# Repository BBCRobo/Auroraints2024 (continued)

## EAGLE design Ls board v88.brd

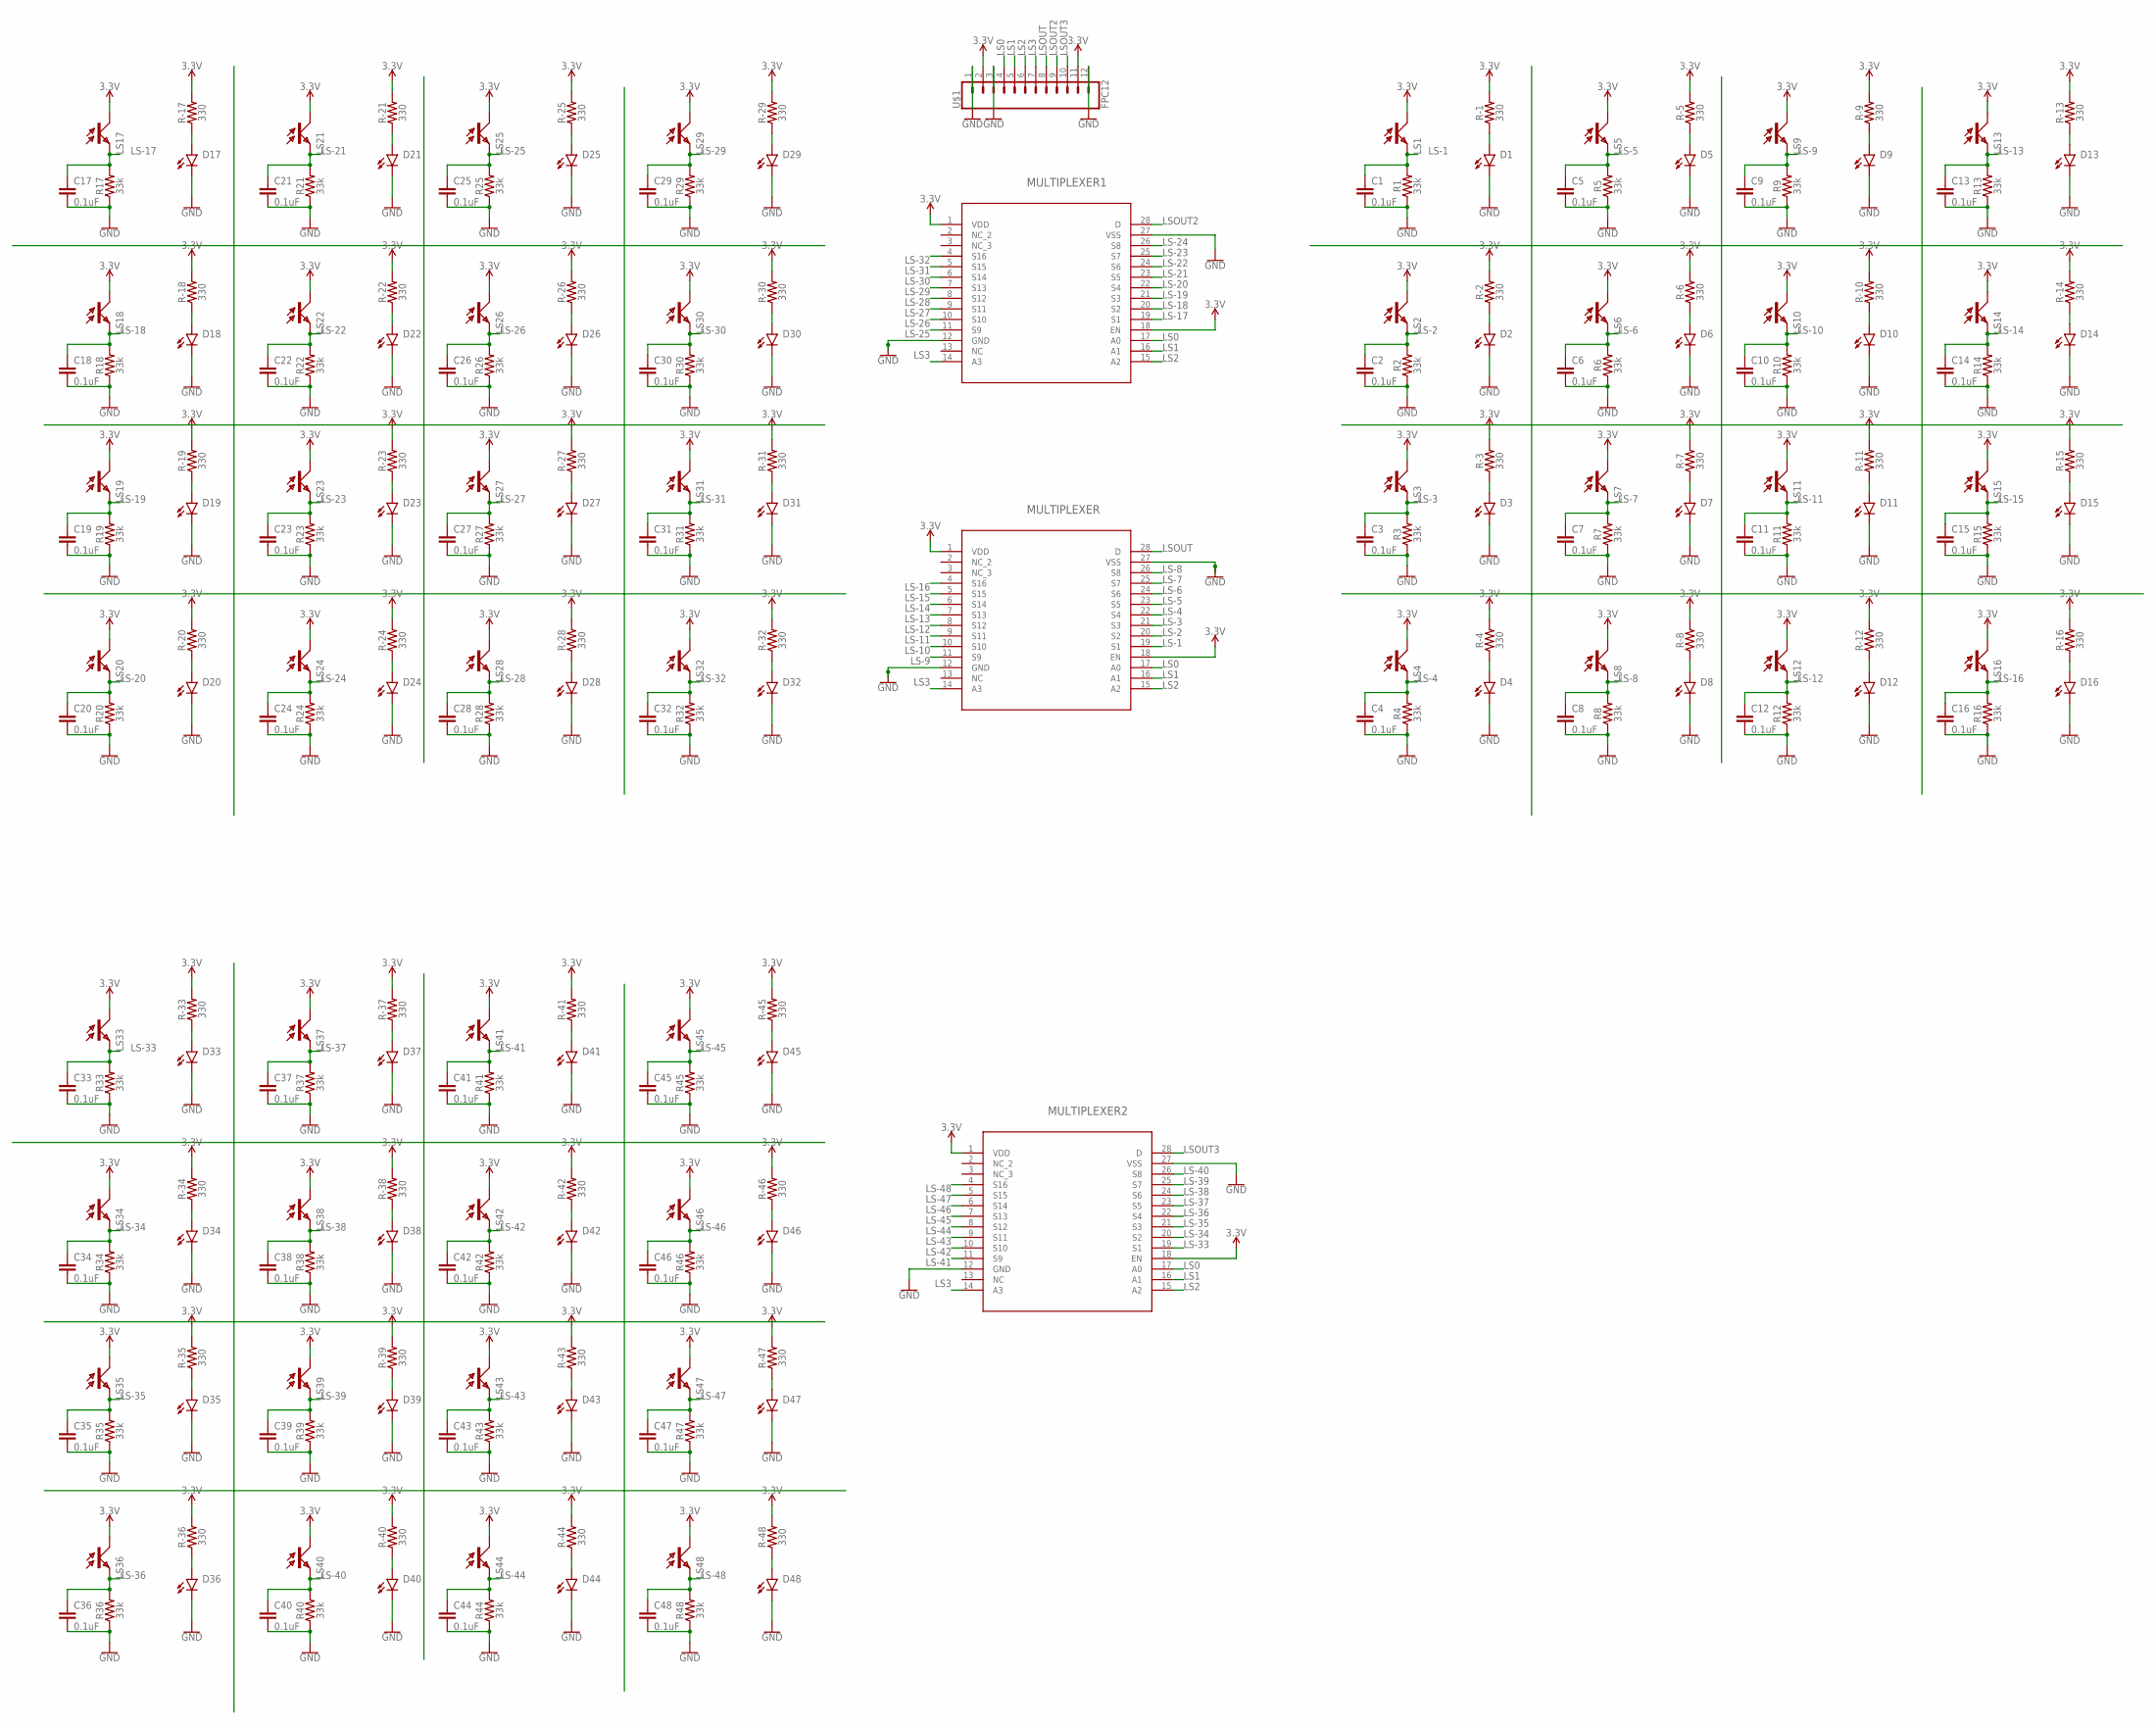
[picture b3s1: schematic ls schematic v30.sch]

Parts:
C1, C2, C3, C4, C5, C6, C7, C8, C9, C10, C11, C12, C13, C14, C15, C16, C17, C18, C19, C20, C21, C22, C23, C24, C25, C26, C27, C28, C29, C30, C31, C32, C33, C34, C35, C36, C37, C38, C39, C40, C41, C42, C43, C44, C45, C46, C47, C48: 0.1uF; 0603
D1, D2, D3, D4, D5, D6, D7, D8, D9, D10, D11, D12, D13, D14, D15, D16, D17, D18, D19, D20, D21, D22, D23, D24, D25, D26, D27, D28, D29, D30, D31, D32, D33, D34, D35, D36, D37, D38, D39, D40, D41, D42, D43, D44, D45, D46, D47, D48: CHIP-FLAT-B_0603-0.35MM; LEDC1608X35N_FLAT-B
LS1, LS2, LS3, LS4, LS5, LS6, LS7, LS8, LS9, LS10, LS11, LS12, LS13, LS14, LS15, LS16, LS17, LS18, LS19, LS20, LS21, LS22, LS23, LS24, LS25, LS26, LS27, LS28, LS29, LS30, LS31, LS32, LS33, LS34, LS35, LS36, LS37, LS38, LS39, LS40, LS41, LS42, LS43, LS44, LS45, LS46, LS47, LS48: ALS; SMD
MULTIPLEXER, MULTIPLEXER1, MULTIPLEXER2: ADG1206YRUZRU_28_ADI-L; RU_28_ADI-L
R1, R2, R3, R4, R5, R6, R7, R8, R9, R10, R11, R12, R13, R14, R15, R16, R17, R18, R19, R20, R21, R22, R23, R24, R25, R26, R27, R28, R29, R30, R31, R32, R33, R34, R35, R36, R37, R38, R39, R40, R41, R42, R43, R44, R45, R46, R47, R48: 33k; 0603
R-1, R-2, R-3, R-4, R-5, R-6, R-7, R-8, R-9, R-10, R-11, R-12, R-13, R-14, R-15, R-16, R-17, R-18, R-19, R-20, R-21, R-22, R-23, R-24, R-25, R-26, R-27, R-28, R-29, R-30, R-31, R-32, R-33, R-34, R-35, R-36, R-37, R-38, R-39, R-40, R-41, R-42, R-43, R-44, R-45, R-46, R-47, R-48: 330; 0603
U$1: FPC12

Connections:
3.3V: LS1.C, LS2.C, LS3.C, LS4.C, LS5.C, LS6.C, LS7.C, LS8.C, LS9.C, LS10.C, LS11.C, LS12.C, LS13.C, LS14.C, LS15.C, LS16.C, LS17.C, LS18.C, LS19.C, LS20.C, LS21.C, LS22.C, LS23.C, LS24.C, LS25.C, LS26.C, LS27.C, LS28.C, LS29.C, LS30.C, LS31.C, LS32.C, LS33.C, LS34.C, LS35.C, LS36.C, LS37.C, LS38.C, LS39.C, LS40.C, LS41.C, LS42.C, LS43.C, LS44.C, LS45.C, LS46.C, LS47.C, LS48.C, MULTIPLEXER.1 (VDD), MULTIPLEXER.18 (EN), MULTIPLEXER1.1 (VDD), MULTIPLEXER1.18 (EN), MULTIPLEXER2.1 (VDD), MULTIPLEXER2.18 (EN), R-1.2, R-2.2, R-3.2, R-4.2, R-5.2, R-6.2, R-7.2, R-8.2, R-9.2, R-10.2, R-11.2, R-12.2, R-13.2, R-14.2, R-15.2, R-16.2, R-17.2, R-18.2, R-19.2, R-20.2, R-21.2, R-22.2, R-23.2, R-24.2, R-25.2, R-26.2, R-27.2, R-28.2, R-29.2, R-30.2, R-31.2, R-32.2, R-33.2, R-34.2, R-35.2, R-36.2, R-37.2, R-38.2, R-39.2, R-40.2, R-41.2, R-42.2, R-43.2, R-44.2, R-45.2, R-46.2, R-47.2, R-48.2, U$1.2, U$1.11
GND: C1.2, C2.2, C3.2, C4.2, C5.2, C6.2, C7.2, C8.2, C9.2, C10.2, C11.2, C12.2, C13.2, C14.2, C15.2, C16.2, C17.2, C18.2, C19.2, C20.2, C21.2, C22.2, C23.2, C24.2, C25.2, C26.2, C27.2, C28.2, C29.2, C30.2, C31.2, C32.2, C33.2, C34.2, C35.2, C36.2, C37.2, C38.2, C39.2, C40.2, C41.2, C42.2, C43.2, C44.2, C45.2, C46.2, C47.2, C48.2, D1.C, D2.C, D3.C, D4.C, D5.C, D6.C, D7.C, D8.C, D9.C, D10.C, D11.C, D12.C, D13.C, D14.C, D15.C, D16.C, D17.C, D18.C, D19.C, D20.C, D21.C, D22.C, D23.C, D24.C, D25.C, D26.C, D27.C, D28.C, D29.C, D30.C, D31.C, D32.C, D33.C, D34.C, D35.C, D36.C, D37.C, D38.C, D39.C, D40.C, D41.C, D42.C, D43.C, D44.C, D45.C, D46.C, D47.C, D48.C, MULTIPLEXER.12 (GND), MULTIPLEXER.27 (VSS), MULTIPLEXER1.12 (GND), MULTIPLEXER1.27 (VSS), MULTIPLEXER2.12 (GND), MULTIPLEXER2.27 (VSS), R1.1, R2.1, R3.1, R4.1, R5.1, R6.1, R7.1, R8.1, R9.1, R10.1, R11.1, R12.1, R13.1, R14.1, R15.1, R16.1, R17.1, R18.1, R19.1, R20.1, R21.1, R22.1, R23.1, R24.1, R25.1, R26.1, R27.1, R28.1, R29.1, R30.1, R31.1, R32.1, R33.1, R34.1, R35.1, R36.1, R37.1, R38.1, R39.1, R40.1, R41.1, R42.1, R43.1, R44.1, R45.1, R46.1, R47.1, R48.1, U$1.1, U$1.3, U$1.12
LS0: MULTIPLEXER.17 (A0), MULTIPLEXER1.17 (A0), MULTIPLEXER2.17 (A0), U$1.4
LS1: MULTIPLEXER.16 (A1), MULTIPLEXER1.16 (A1), MULTIPLEXER2.16 (A1), U$1.5
LS2: MULTIPLEXER.15 (A2), MULTIPLEXER1.15 (A2), MULTIPLEXER2.15 (A2), U$1.6
LS3: MULTIPLEXER.14 (A3), MULTIPLEXER1.14 (A3), MULTIPLEXER2.14 (A3), U$1.7
LS-1: C1.1, LS1.E, MULTIPLEXER.19 (S1), R1.2
LS-2: C2.1, LS2.E, MULTIPLEXER.20 (S2), R2.2
LS-3: C3.1, LS3.E, MULTIPLEXER.21 (S3), R3.2
LS-4: C4.1, LS4.E, MULTIPLEXER.22 (S4), R4.2
LS-5: C5.1, LS5.E, MULTIPLEXER.23 (S5), R5.2
LS-6: C6.1, LS6.E, MULTIPLEXER.24 (S6), R6.2
LS-7: C7.1, LS7.E, MULTIPLEXER.25 (S7), R7.2
LS-8: C8.1, LS8.E, MULTIPLEXER.26 (S8), R8.2
LS-9: C9.1, LS9.E, MULTIPLEXER.11 (S9), R9.2
LS-10: C10.1, LS10.E, MULTIPLEXER.10 (S10), R10.2
LS-11: C11.1, LS11.E, MULTIPLEXER.9 (S11), R11.2
LS-12: C12.1, LS12.E, MULTIPLEXER.8 (S12), R12.2
LS-13: C13.1, LS13.E, MULTIPLEXER.7 (S13), R13.2
LS-14: C14.1, LS14.E, MULTIPLEXER.6 (S14), R14.2
LS-15: C15.1, LS15.E, MULTIPLEXER.5 (S15), R15.2
LS-16: C16.1, LS16.E, MULTIPLEXER.4 (S16), R16.2
LS-17: C17.1, LS17.E, MULTIPLEXER1.19 (S1), R17.2
LS-18: C18.1, LS18.E, MULTIPLEXER1.20 (S2), R18.2
LS-19: C19.1, LS19.E, MULTIPLEXER1.21 (S3), R19.2
LS-20: C20.1, LS20.E, MULTIPLEXER1.22 (S4), R20.2
LS-21: C21.1, LS21.E, MULTIPLEXER1.23 (S5), R21.2
LS-22: C22.1, LS22.E, MULTIPLEXER1.24 (S6), R22.2
LS-23: C23.1, LS23.E, MULTIPLEXER1.25 (S7), R23.2
LS-24: C24.1, LS24.E, MULTIPLEXER1.26 (S8), R24.2
LS-25: C25.1, LS25.E, MULTIPLEXER1.11 (S9), R25.2
LS-26: C26.1, LS26.E, MULTIPLEXER1.10 (S10), R26.2
LS-27: C27.1, LS27.E, MULTIPLEXER1.9 (S11), R27.2
LS-28: C28.1, LS28.E, MULTIPLEXER1.8 (S12), R28.2
LS-29: C29.1, LS29.E, MULTIPLEXER1.7 (S13), R29.2
LS-30: C30.1, LS30.E, MULTIPLEXER1.6 (S14), R30.2
LS-31: C31.1, LS31.E, MULTIPLEXER1.5 (S15), R31.2
LS-32: C32.1, LS32.E, MULTIPLEXER1.4 (S16), R32.2
LS-33: C33.1, LS33.E, MULTIPLEXER2.19 (S1), R33.2
LS-34: C34.1, LS34.E, MULTIPLEXER2.20 (S2), R34.2
LS-35: C35.1, LS35.E, MULTIPLEXER2.21 (S3), R35.2
LS-36: C36.1, LS36.E, MULTIPLEXER2.22 (S4), R36.2
LS-37: C37.1, LS37.E, MULTIPLEXER2.23 (S5), R37.2
LS-38: C38.1, LS38.E, MULTIPLEXER2.24 (S6), R38.2
LS-39: C39.1, LS39.E, MULTIPLEXER2.25 (S7), R39.2
LS-40: C40.1, LS40.E, MULTIPLEXER2.26 (S8), R40.2
LS-41: C41.1, LS41.E, MULTIPLEXER2.11 (S9), R41.2
LS-42: C42.1, LS42.E, MULTIPLEXER2.10 (S10), R42.2
LS-43: C43.1, LS43.E, MULTIPLEXER2.9 (S11), R43.2
LS-44: C44.1, LS44.E, MULTIPLEXER2.8 (S12), R44.2
LS-45: C45.1, LS45.E, MULTIPLEXER2.7 (S13), R45.2
LS-46: C46.1, LS46.E, MULTIPLEXER2.6 (S14), R46.2
LS-47: C47.1, LS47.E, MULTIPLEXER2.5 (S15), R47.2
LS-48: C48.1, LS48.E, MULTIPLEXER2.4 (S16), R48.2
LSOUT: MULTIPLEXER.28 (D), U$1.8
LSOUT2: MULTIPLEXER1.28 (D), U$1.9
LSOUT3: MULTIPLEXER2.28 (D), U$1.10
unnamed: D1.A, R-1.1
unnamed: D2.A, R-2.1
unnamed: D3.A, R-3.1
unnamed: D4.A, R-4.1
unnamed: D5.A, R-5.1
unnamed: D6.A, R-6.1
unnamed: D7.A, R-7.1
unnamed: D8.A, R-8.1
unnamed: D9.A, R-9.1
unnamed: D10.A, R-10.1
unnamed: D11.A, R-11.1
unnamed: D12.A, R-12.1
unnamed: D13.A, R-13.1
unnamed: D14.A, R-14.1
unnamed: D15.A, R-15.1
unnamed: D16.A, R-16.1
unnamed: D17.A, R-17.1
unnamed: D18.A, R-18.1
unnamed: D19.A, R-19.1
unnamed: D20.A, R-20.1
unnamed: D21.A, R-21.1
unnamed: D22.A, R-22.1
unnamed: D23.A, R-23.1
unnamed: D24.A, R-24.1
unnamed: D25.A, R-25.1
unnamed: D26.A, R-26.1
unnamed: D27.A, R-27.1
unnamed: D33.A, R-33.1
unnamed: D34.A, R-34.1
unnamed: D35.A, R-35.1
unnamed: D36.A, R-36.1
unnamed: D37.A, R-37.1
unnamed: D28.A, R-28.1
unnamed: D29.A, R-29.1
unnamed: D30.A, R-30.1
unnamed: D31.A, R-31.1
unnamed: D32.A, R-32.1
unnamed: D38.A, R-38.1
unnamed: D39.A, R-39.1
unnamed: D40.A, R-40.1
unnamed: D41.A, R-41.1
unnamed: D42.A, R-42.1
unnamed: D43.A, R-43.1
unnamed: D44.A, R-44.1
unnamed: D45.A, R-45.1
unnamed: D46.A, R-46.1
unnamed: D47.A, R-47.1
unnamed: D48.A, R-48.1

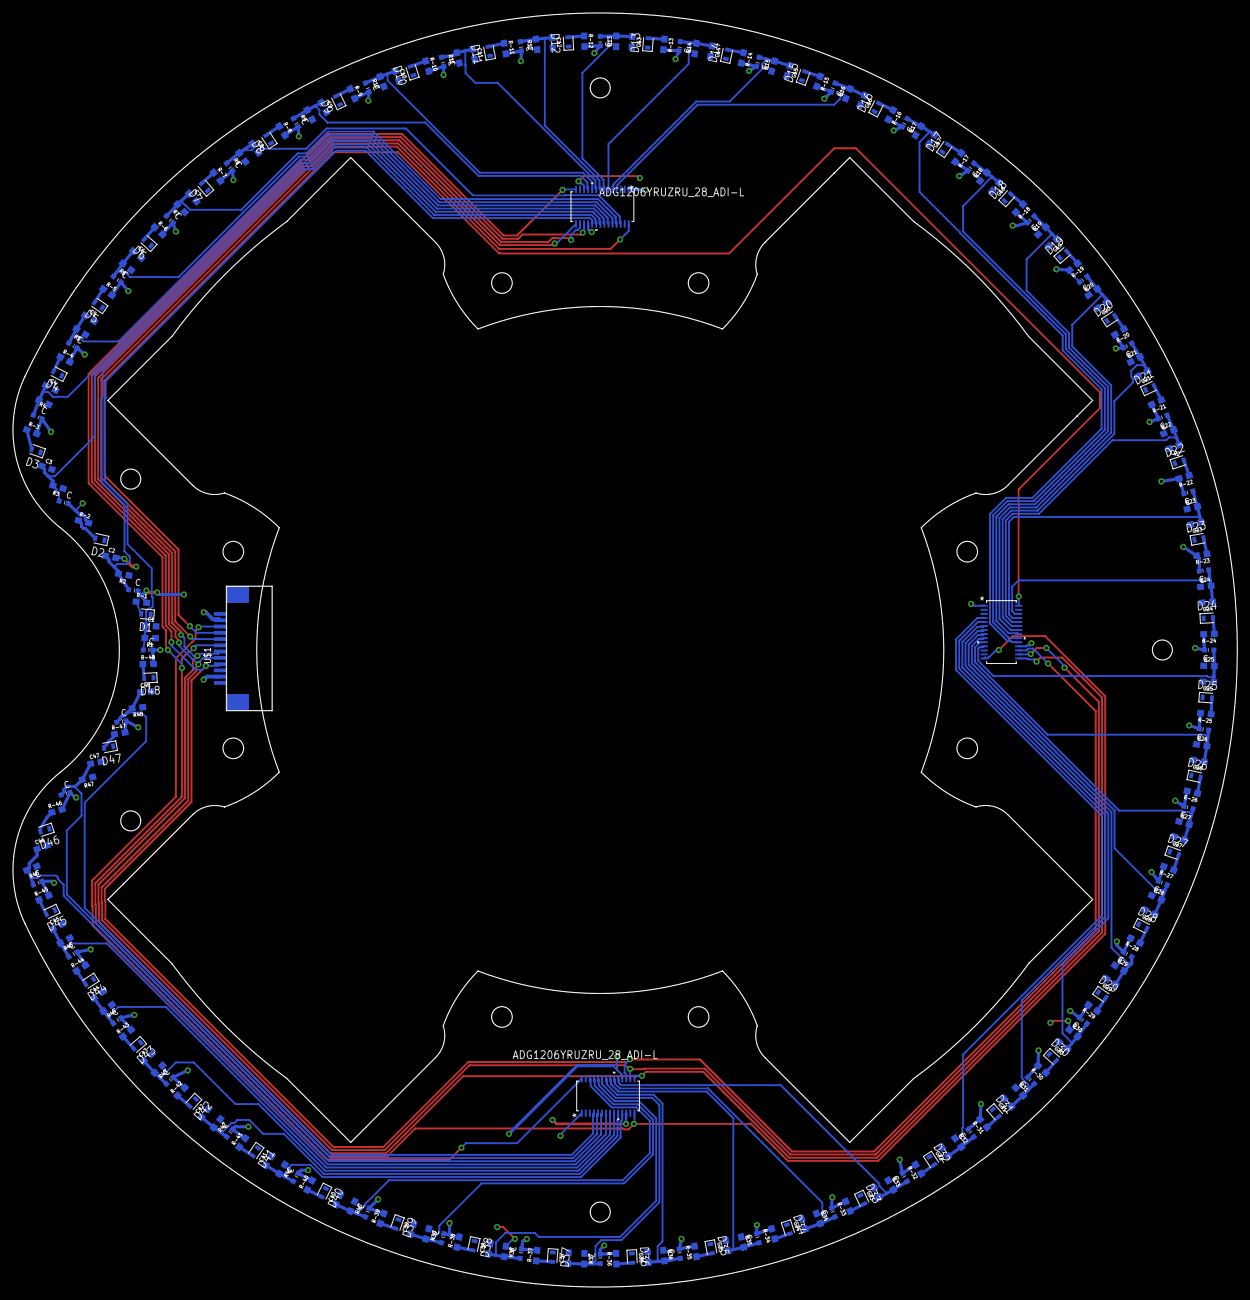
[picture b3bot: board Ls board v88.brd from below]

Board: 2 copper layers, 196.0 x 204.0 mm, 244 parts (244 on the bottom side), 105 nets.

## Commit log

2024-07-02 README.md
